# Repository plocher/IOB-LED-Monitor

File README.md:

# IOB-LED-Monitor
## License: CERN Open Hardware Licence v1.2

IOB LED Monitor daughterboard

Active-Low LED monitor for I/O pin signal debugging.
(LED is on when pin is 0v, off when pin is at Vcc)

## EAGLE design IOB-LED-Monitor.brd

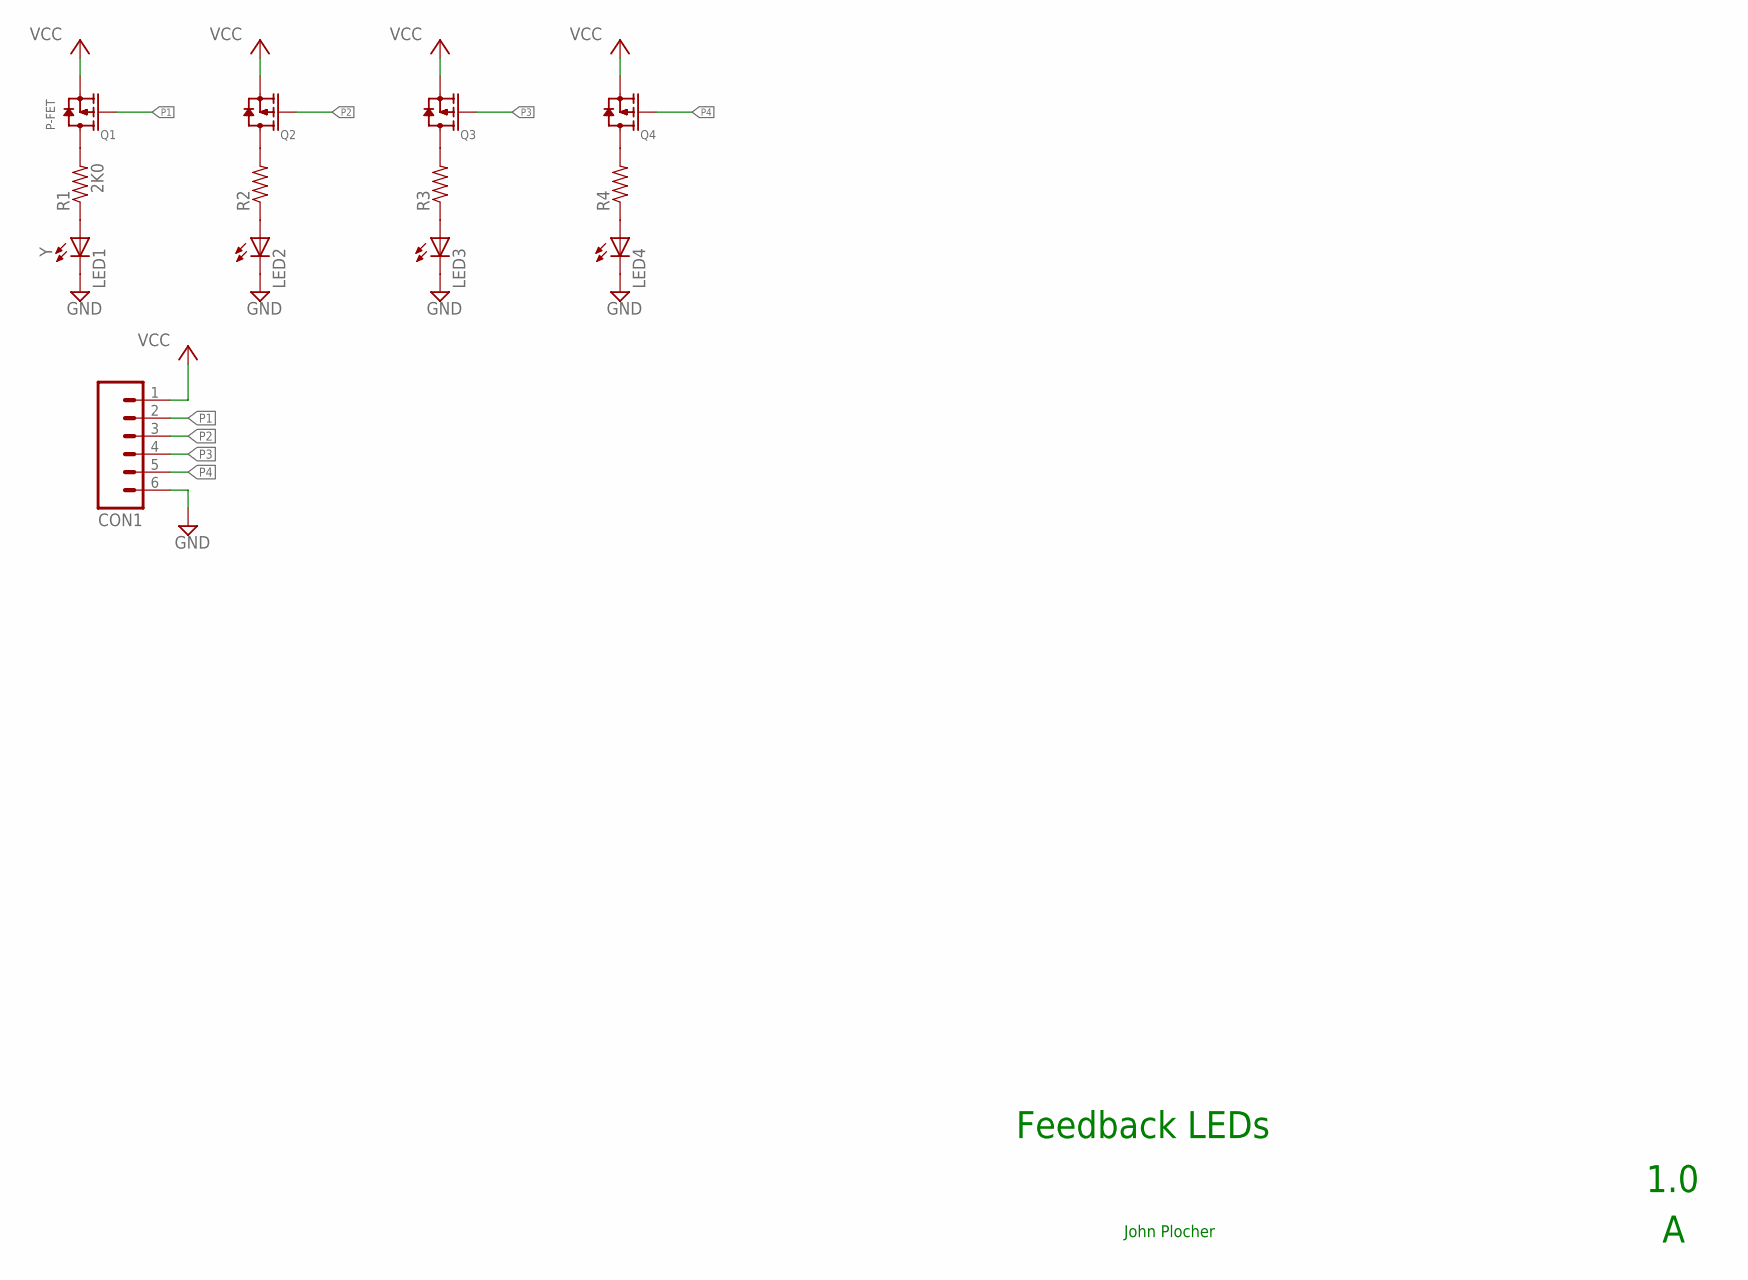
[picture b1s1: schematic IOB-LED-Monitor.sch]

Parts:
CON1: CONNECTOR-M06LOCK; 1X06_LOCK
LED1, LED2, LED3, LED4: Y; 0603-LED
Q1, Q2, Q3, Q4: P-FET; SOT23
R1, R2, R3, R4: 2K0; 0805-RES

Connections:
GND: CON1.6, LED1.C, LED2.C, LED3.C, LED4.C
unnamed: Q1.3 (D), R1.2
unnamed: Q2.3 (D), R2.2
unnamed: Q3.3 (D), R3.2
unnamed: Q4.3 (D), R4.2
unnamed: LED1.A, R1.1
unnamed: LED2.A, R2.1
unnamed: LED3.A, R3.1
unnamed: LED4.A, R4.1
P1: CON1.2, Q1.1 (G)
P2: CON1.3, Q2.1 (G)
P3: CON1.4, Q3.1 (G)
P4: CON1.5, Q4.1 (G)
VCC: CON1.1, Q1.2 (S), Q2.2 (S), Q3.2 (S), Q4.2 (S)

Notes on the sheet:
Feedback LEDs
1.0
John Plocher

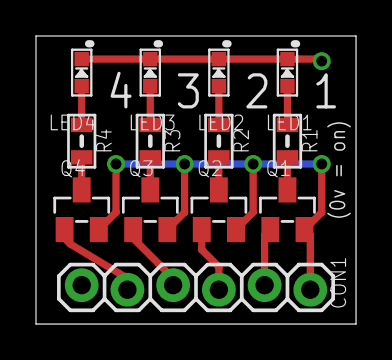
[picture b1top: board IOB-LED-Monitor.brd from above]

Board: 2 copper layers, 17.8 x 16.0 mm, 13 parts (0 on the bottom side), 14 nets.

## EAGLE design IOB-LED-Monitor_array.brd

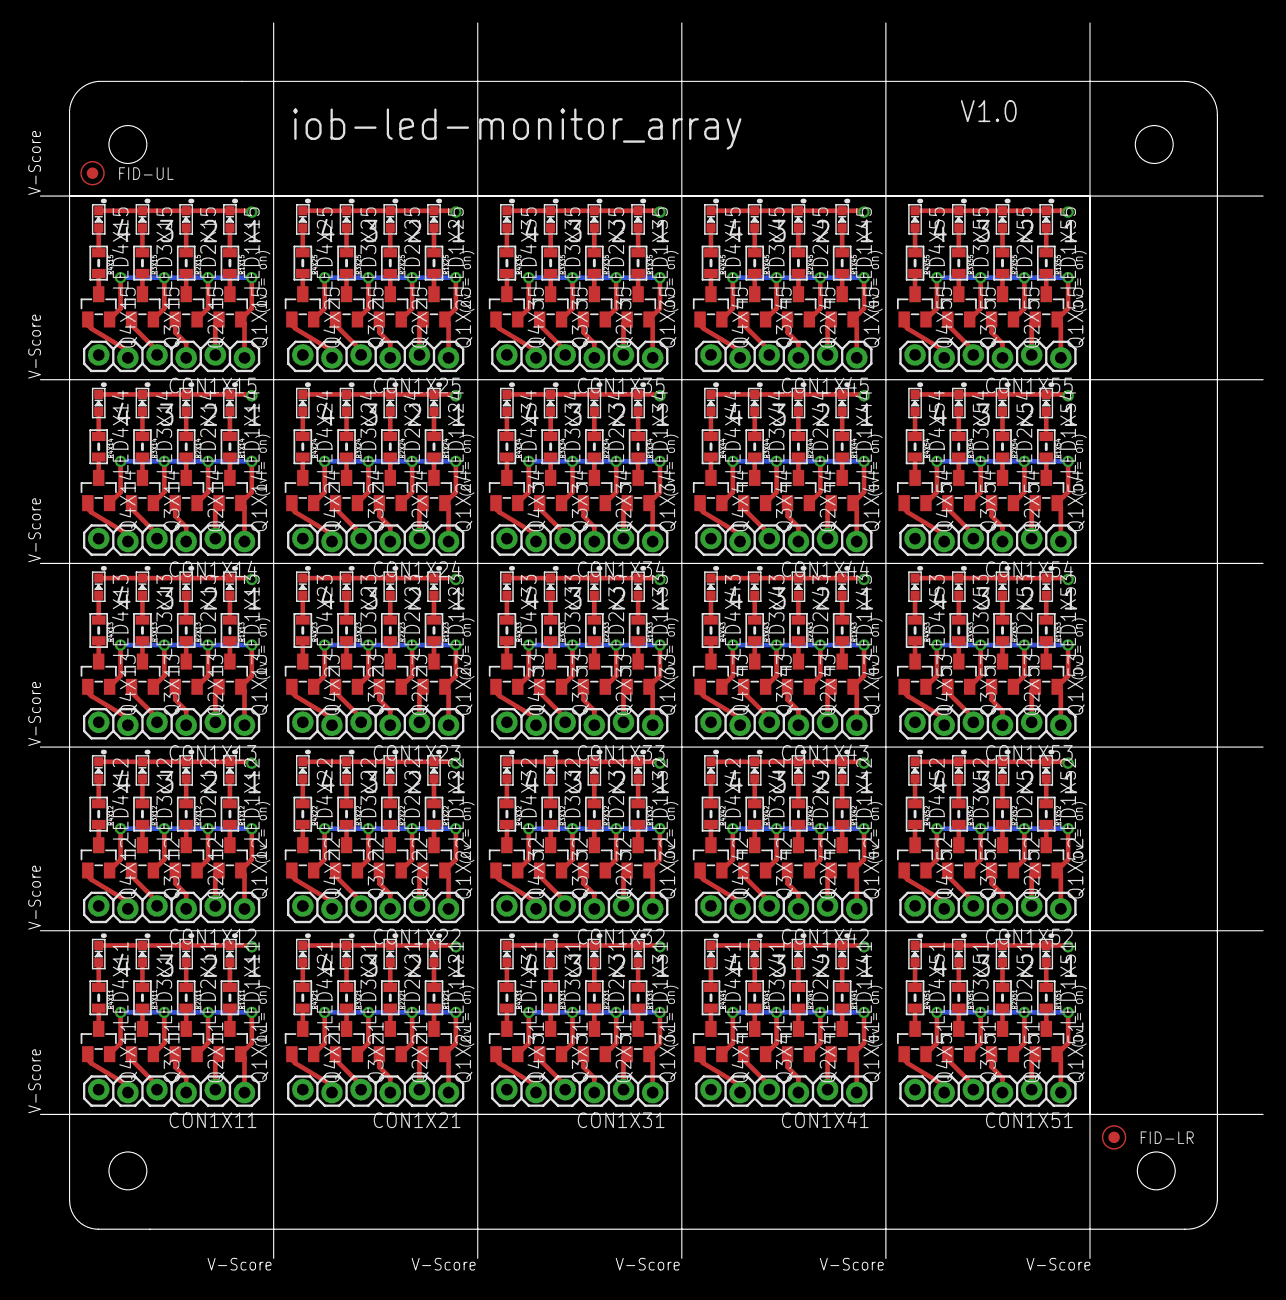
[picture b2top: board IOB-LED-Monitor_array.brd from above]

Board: 2 copper layers, 108.0 x 109.3 mm, 328 parts (0 on the bottom side), 350 nets.

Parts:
CON1X11, CON1X12, CON1X13, CON1X14, CON1X15, CON1X21, CON1X22, CON1X23, CON1X24, CON1X25, CON1X31, CON1X32, CON1X33, CON1X34, CON1X35, CON1X41, CON1X42, CON1X43, CON1X44, CON1X45, CON1X51, CON1X52, CON1X53, CON1X54, CON1X55: 1X06_LOCK
FID-LR: FIDUCIAL_1MM
FID-UL: FIDUCIAL_1MM
LED1X11, LED1X12, LED1X13, LED1X14, LED1X15, LED1X21, LED1X22, LED1X23, LED1X24, LED1X25, LED1X31, LED1X32, LED1X33, LED1X34, LED1X35, LED1X41, LED1X42, LED1X43, LED1X44, LED1X45, LED1X51, LED1X52, LED1X53, LED1X54, LED1X55, LED2X11, LED2X12, LED2X13, LED2X14, LED2X15, LED2X21, LED2X22, LED2X23, LED2X24, LED2X25, LED2X31, LED2X32, LED2X33, LED2X34, LED2X35, LED2X41, LED2X42, LED2X43, LED2X44, LED2X45, LED2X51, LED2X52, LED2X53, LED2X54, LED2X55, LED3X11, LED3X12, LED3X13, LED3X14, LED3X15, LED3X21, LED3X22, LED3X23, LED3X24, LED3X25, LED3X31, LED3X32, LED3X33, LED3X34, LED3X35, LED3X41, LED3X42, LED3X43, LED3X44, LED3X45, LED3X51, LED3X52, LED3X53, LED3X54, LED3X55, LED4X11, LED4X12, LED4X13, LED4X14, LED4X15, LED4X21, LED4X22, LED4X23, LED4X24, LED4X25, LED4X31, LED4X32, LED4X33, LED4X34, LED4X35, LED4X41, LED4X42, LED4X43, LED4X44, LED4X45, LED4X51, LED4X52, LED4X53, LED4X54, LED4X55: Y; 0603-LED
Q1X11, Q1X12, Q1X13, Q1X14, Q1X15, Q1X21, Q1X22, Q1X23, Q1X24, Q1X25, Q1X31, Q1X32, Q1X33, Q1X34, Q1X35, Q1X41, Q1X42, Q1X43, Q1X44, Q1X45, Q1X51, Q1X52, Q1X53, Q1X54, Q1X55, Q2X11, Q2X12, Q2X13, Q2X14, Q2X15, Q2X21, Q2X22, Q2X23, Q2X24, Q2X25, Q2X31, Q2X32, Q2X33, Q2X34, Q2X35, Q2X41, Q2X42, Q2X43, Q2X44, Q2X45, Q2X51, Q2X52, Q2X53, Q2X54, Q2X55, Q3X11, Q3X12, Q3X13, Q3X14, Q3X15, Q3X21, Q3X22, Q3X23, Q3X24, Q3X25, Q3X31, Q3X32, Q3X33, Q3X34, Q3X35, Q3X41, Q3X42, Q3X43, Q3X44, Q3X45, Q3X51, Q3X52, Q3X53, Q3X54, Q3X55, Q4X11, Q4X12, Q4X13, Q4X14, Q4X15, Q4X21, Q4X22, Q4X23, Q4X24, Q4X25, Q4X31, Q4X32, Q4X33, Q4X34, Q4X35, Q4X41, Q4X42, Q4X43, Q4X44, Q4X45, Q4X51, Q4X52, Q4X53, Q4X54, Q4X55: P-FET; SOT23
R1X11, R1X12, R1X13, R1X14, R1X15, R1X21, R1X22, R1X23, R1X24, R1X25, R1X31, R1X32, R1X33, R1X34, R1X35, R1X41, R1X42, R1X43, R1X44, R1X45, R1X51, R1X52, R1X53, R1X54, R1X55, R2X11, R2X12, R2X13, R2X14, R2X15, R2X21, R2X22, R2X23, R2X24, R2X25, R2X31, R2X32, R2X33, R2X34, R2X35, R2X41, R2X42, R2X43, R2X44, R2X45, R2X51, R2X52, R2X53, R2X54, R2X55, R3X11, R3X12, R3X13, R3X14, R3X15, R3X21, R3X22, R3X23, R3X24, R3X25, R3X31, R3X32, R3X33, R3X34, R3X35, R3X41, R3X42, R3X43, R3X44, R3X45, R3X51, R3X52, R3X53, R3X54, R3X55, R4X11, R4X12, R4X13, R4X14, R4X15, R4X21, R4X22, R4X23, R4X24, R4X25, R4X31, R4X32, R4X33, R4X34, R4X35, R4X41, R4X42, R4X43, R4X44, R4X45, R4X51, R4X52, R4X53, R4X54, R4X55: 2K0; 0805-RES
R4X1: BOARD-SEEED10X10

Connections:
GNDX11: CON1X11.6, LED1X11.C, LED2X11.C, LED3X11.C, LED4X11.C
GNDX12: CON1X12.6, LED1X12.C, LED2X12.C, LED3X12.C, LED4X12.C
GNDX13: CON1X13.6, LED1X13.C, LED2X13.C, LED3X13.C, LED4X13.C
GNDX14: CON1X14.6, LED1X14.C, LED2X14.C, LED3X14.C, LED4X14.C
GNDX15: CON1X15.6, LED1X15.C, LED2X15.C, LED3X15.C, LED4X15.C
GNDX21: CON1X21.6, LED1X21.C, LED2X21.C, LED3X21.C, LED4X21.C
GNDX22: CON1X22.6, LED1X22.C, LED2X22.C, LED3X22.C, LED4X22.C
GNDX23: CON1X23.6, LED1X23.C, LED2X23.C, LED3X23.C, LED4X23.C
GNDX24: CON1X24.6, LED1X24.C, LED2X24.C, LED3X24.C, LED4X24.C
GNDX25: CON1X25.6, LED1X25.C, LED2X25.C, LED3X25.C, LED4X25.C
GNDX31: CON1X31.6, LED1X31.C, LED2X31.C, LED3X31.C, LED4X31.C
GNDX32: CON1X32.6, LED1X32.C, LED2X32.C, LED3X32.C, LED4X32.C
GNDX33: CON1X33.6, LED1X33.C, LED2X33.C, LED3X33.C, LED4X33.C
GNDX34: CON1X34.6, LED1X34.C, LED2X34.C, LED3X34.C, LED4X34.C
GNDX35: CON1X35.6, LED1X35.C, LED2X35.C, LED3X35.C, LED4X35.C
GNDX41: CON1X41.6, LED1X41.C, LED2X41.C, LED3X41.C, LED4X41.C
GNDX42: CON1X42.6, LED1X42.C, LED2X42.C, LED3X42.C, LED4X42.C
GNDX43: CON1X43.6, LED1X43.C, LED2X43.C, LED3X43.C, LED4X43.C
GNDX44: CON1X44.6, LED1X44.C, LED2X44.C, LED3X44.C, LED4X44.C
GNDX45: CON1X45.6, LED1X45.C, LED2X45.C, LED3X45.C, LED4X45.C
GNDX51: CON1X51.6, LED1X51.C, LED2X51.C, LED3X51.C, LED4X51.C
GNDX52: CON1X52.6, LED1X52.C, LED2X52.C, LED3X52.C, LED4X52.C
GNDX53: CON1X53.6, LED1X53.C, LED2X53.C, LED3X53.C, LED4X53.C
GNDX54: CON1X54.6, LED1X54.C, LED2X54.C, LED3X54.C, LED4X54.C
GNDX55: CON1X55.6, LED1X55.C, LED2X55.C, LED3X55.C, LED4X55.C
unnamed: Q1X11.3, R1X11.2
unnamed: Q1X12.3, R1X12.2
unnamed: Q1X13.3, R1X13.2
unnamed: Q1X14.3, R1X14.2
unnamed: Q1X15.3, R1X15.2
unnamed: Q1X21.3, R1X21.2
unnamed: Q1X22.3, R1X22.2
unnamed: Q1X23.3, R1X23.2
unnamed: Q1X24.3, R1X24.2
unnamed: Q1X25.3, R1X25.2
unnamed: Q1X31.3, R1X31.2
unnamed: Q1X32.3, R1X32.2
unnamed: Q1X33.3, R1X33.2
unnamed: Q1X34.3, R1X34.2
unnamed: Q1X35.3, R1X35.2
unnamed: Q1X41.3, R1X41.2
unnamed: Q1X42.3, R1X42.2
unnamed: Q1X43.3, R1X43.2
unnamed: Q1X44.3, R1X44.2
unnamed: Q1X45.3, R1X45.2
unnamed: Q1X51.3, R1X51.2
unnamed: Q1X52.3, R1X52.2
unnamed: Q1X53.3, R1X53.2
unnamed: Q1X54.3, R1X54.2
unnamed: Q1X55.3, R1X55.2
unnamed: Q2X11.3, R2X11.2
unnamed: Q2X12.3, R2X12.2
unnamed: Q2X13.3, R2X13.2
unnamed: Q2X14.3, R2X14.2
unnamed: Q2X15.3, R2X15.2
unnamed: Q2X21.3, R2X21.2
unnamed: Q2X22.3, R2X22.2
unnamed: Q2X23.3, R2X23.2
unnamed: Q2X24.3, R2X24.2
unnamed: Q2X25.3, R2X25.2
unnamed: Q2X31.3, R2X31.2
unnamed: Q2X32.3, R2X32.2
unnamed: Q2X33.3, R2X33.2
unnamed: Q2X34.3, R2X34.2
unnamed: Q2X35.3, R2X35.2
unnamed: Q2X41.3, R2X41.2
unnamed: Q2X42.3, R2X42.2
unnamed: Q2X43.3, R2X43.2
unnamed: Q2X44.3, R2X44.2
unnamed: Q2X45.3, R2X45.2
unnamed: Q2X51.3, R2X51.2
unnamed: Q2X52.3, R2X52.2
unnamed: Q2X53.3, R2X53.2
unnamed: Q2X54.3, R2X54.2
unnamed: Q2X55.3, R2X55.2
unnamed: Q3X11.3, R3X11.2
unnamed: Q3X12.3, R3X12.2
unnamed: Q3X13.3, R3X13.2
unnamed: Q3X14.3, R3X14.2
unnamed: Q3X15.3, R3X15.2
unnamed: Q3X21.3, R3X21.2
unnamed: Q3X22.3, R3X22.2
unnamed: Q3X23.3, R3X23.2
unnamed: Q3X24.3, R3X24.2
unnamed: Q3X25.3, R3X25.2
unnamed: Q3X31.3, R3X31.2
unnamed: Q3X32.3, R3X32.2
unnamed: Q3X33.3, R3X33.2
unnamed: Q3X34.3, R3X34.2
unnamed: Q3X35.3, R3X35.2
unnamed: Q3X41.3, R3X41.2
unnamed: Q3X42.3, R3X42.2
unnamed: Q3X43.3, R3X43.2
unnamed: Q3X44.3, R3X44.2
unnamed: Q3X45.3, R3X45.2
unnamed: Q3X51.3, R3X51.2
unnamed: Q3X52.3, R3X52.2
unnamed: Q3X53.3, R3X53.2
unnamed: Q3X54.3, R3X54.2
unnamed: Q3X55.3, R3X55.2
unnamed: Q4X11.3, R4X11.2
unnamed: Q4X12.3, R4X12.2
unnamed: Q4X13.3, R4X13.2
unnamed: Q4X14.3, R4X14.2
unnamed: Q4X15.3, R4X15.2
unnamed: Q4X21.3, R4X21.2
unnamed: Q4X22.3, R4X22.2
unnamed: Q4X23.3, R4X23.2
unnamed: Q4X24.3, R4X24.2
unnamed: Q4X25.3, R4X25.2
unnamed: Q4X31.3, R4X31.2
unnamed: Q4X32.3, R4X32.2
unnamed: Q4X33.3, R4X33.2
unnamed: Q4X34.3, R4X34.2
unnamed: Q4X35.3, R4X35.2
unnamed: Q4X41.3, R4X41.2
unnamed: Q4X42.3, R4X42.2
unnamed: Q4X43.3, R4X43.2
unnamed: Q4X44.3, R4X44.2
unnamed: Q4X45.3, R4X45.2
unnamed: Q4X51.3, R4X51.2
unnamed: Q4X52.3, R4X52.2
unnamed: Q4X53.3, R4X53.2
unnamed: Q4X54.3, R4X54.2
unnamed: Q4X55.3, R4X55.2
unnamed: LED1X11.A, R1X11.1
unnamed: LED1X12.A, R1X12.1
unnamed: LED1X13.A, R1X13.1
unnamed: LED1X14.A, R1X14.1
unnamed: LED1X15.A, R1X15.1
unnamed: LED1X21.A, R1X21.1
unnamed: LED1X22.A, R1X22.1
unnamed: LED1X23.A, R1X23.1
unnamed: LED1X24.A, R1X24.1
unnamed: LED1X25.A, R1X25.1
unnamed: LED1X31.A, R1X31.1
unnamed: LED1X32.A, R1X32.1
unnamed: LED1X33.A, R1X33.1
unnamed: LED1X34.A, R1X34.1
unnamed: LED1X35.A, R1X35.1
unnamed: LED1X41.A, R1X41.1
unnamed: LED1X42.A, R1X42.1
unnamed: LED1X43.A, R1X43.1
unnamed: LED1X44.A, R1X44.1
unnamed: LED1X45.A, R1X45.1
unnamed: LED1X51.A, R1X51.1
unnamed: LED1X52.A, R1X52.1
unnamed: LED1X53.A, R1X53.1
unnamed: LED1X54.A, R1X54.1
unnamed: LED1X55.A, R1X55.1
unnamed: LED2X11.A, R2X11.1
unnamed: LED2X12.A, R2X12.1
unnamed: LED2X13.A, R2X13.1
unnamed: LED2X14.A, R2X14.1
unnamed: LED2X15.A, R2X15.1
unnamed: LED2X21.A, R2X21.1
unnamed: LED2X22.A, R2X22.1
unnamed: LED2X23.A, R2X23.1
unnamed: LED2X24.A, R2X24.1
unnamed: LED2X25.A, R2X25.1
unnamed: LED2X31.A, R2X31.1
unnamed: LED2X32.A, R2X32.1
unnamed: LED2X33.A, R2X33.1
unnamed: LED2X34.A, R2X34.1
unnamed: LED2X35.A, R2X35.1
unnamed: LED2X41.A, R2X41.1
unnamed: LED2X42.A, R2X42.1
unnamed: LED2X43.A, R2X43.1
unnamed: LED2X44.A, R2X44.1
unnamed: LED2X45.A, R2X45.1
unnamed: LED2X51.A, R2X51.1
unnamed: LED2X52.A, R2X52.1
unnamed: LED2X53.A, R2X53.1
unnamed: LED2X54.A, R2X54.1
unnamed: LED2X55.A, R2X55.1
unnamed: LED3X11.A, R3X11.1
unnamed: LED3X12.A, R3X12.1
unnamed: LED3X13.A, R3X13.1
unnamed: LED3X14.A, R3X14.1
unnamed: LED3X15.A, R3X15.1
unnamed: LED3X21.A, R3X21.1
unnamed: LED3X22.A, R3X22.1
unnamed: LED3X23.A, R3X23.1
unnamed: LED3X24.A, R3X24.1
unnamed: LED3X25.A, R3X25.1
unnamed: LED3X31.A, R3X31.1
unnamed: LED3X32.A, R3X32.1
unnamed: LED3X33.A, R3X33.1
unnamed: LED3X34.A, R3X34.1
unnamed: LED3X35.A, R3X35.1
unnamed: LED3X41.A, R3X41.1
unnamed: LED3X42.A, R3X42.1
unnamed: LED3X43.A, R3X43.1
unnamed: LED3X44.A, R3X44.1
unnamed: LED3X45.A, R3X45.1
unnamed: LED3X51.A, R3X51.1
unnamed: LED3X52.A, R3X52.1
unnamed: LED3X53.A, R3X53.1
unnamed: LED3X54.A, R3X54.1
unnamed: LED3X55.A, R3X55.1
unnamed: LED4X11.A, R4X11.1
unnamed: LED4X12.A, R4X12.1
unnamed: LED4X13.A, R4X13.1
unnamed: LED4X14.A, R4X14.1
unnamed: LED4X15.A, R4X15.1
unnamed: LED4X21.A, R4X21.1
unnamed: LED4X22.A, R4X22.1
unnamed: LED4X23.A, R4X23.1
unnamed: LED4X24.A, R4X24.1
unnamed: LED4X25.A, R4X25.1
unnamed: LED4X31.A, R4X31.1
unnamed: LED4X32.A, R4X32.1
unnamed: LED4X33.A, R4X33.1
unnamed: LED4X34.A, R4X34.1
unnamed: LED4X35.A, R4X35.1
unnamed: LED4X41.A, R4X41.1
unnamed: LED4X42.A, R4X42.1
unnamed: LED4X43.A, R4X43.1
unnamed: LED4X44.A, R4X44.1
unnamed: LED4X45.A, R4X45.1
unnamed: LED4X51.A, R4X51.1
unnamed: LED4X52.A, R4X52.1
unnamed: LED4X53.A, R4X53.1
unnamed: LED4X54.A, R4X54.1
unnamed: LED4X55.A, R4X55.1
P1X11: CON1X11.2, Q1X11.1
P1X12: CON1X12.2, Q1X12.1
P1X13: CON1X13.2, Q1X13.1
P1X14: CON1X14.2, Q1X14.1
P1X15: CON1X15.2, Q1X15.1
P1X21: CON1X21.2, Q1X21.1
P1X22: CON1X22.2, Q1X22.1
P1X23: CON1X23.2, Q1X23.1
P1X24: CON1X24.2, Q1X24.1
P1X25: CON1X25.2, Q1X25.1
P1X31: CON1X31.2, Q1X31.1
P1X32: CON1X32.2, Q1X32.1
P1X33: CON1X33.2, Q1X33.1
P1X34: CON1X34.2, Q1X34.1
P1X35: CON1X35.2, Q1X35.1
P1X41: CON1X41.2, Q1X41.1
P1X42: CON1X42.2, Q1X42.1
P1X43: CON1X43.2, Q1X43.1
P1X44: CON1X44.2, Q1X44.1
P1X45: CON1X45.2, Q1X45.1
P1X51: CON1X51.2, Q1X51.1
P1X52: CON1X52.2, Q1X52.1
P1X53: CON1X53.2, Q1X53.1
P1X54: CON1X54.2, Q1X54.1
P1X55: CON1X55.2, Q1X55.1
P2X11: CON1X11.3, Q2X11.1
P2X12: CON1X12.3, Q2X12.1
P2X13: CON1X13.3, Q2X13.1
P2X14: CON1X14.3, Q2X14.1
P2X15: CON1X15.3, Q2X15.1
P2X21: CON1X21.3, Q2X21.1
P2X22: CON1X22.3, Q2X22.1
P2X23: CON1X23.3, Q2X23.1
P2X24: CON1X24.3, Q2X24.1
P2X25: CON1X25.3, Q2X25.1
P2X31: CON1X31.3, Q2X31.1
P2X32: CON1X32.3, Q2X32.1
P2X33: CON1X33.3, Q2X33.1
P2X34: CON1X34.3, Q2X34.1
P2X35: CON1X35.3, Q2X35.1
P2X41: CON1X41.3, Q2X41.1
P2X42: CON1X42.3, Q2X42.1
P2X43: CON1X43.3, Q2X43.1
P2X44: CON1X44.3, Q2X44.1
P2X45: CON1X45.3, Q2X45.1
P2X51: CON1X51.3, Q2X51.1
P2X52: CON1X52.3, Q2X52.1
P2X53: CON1X53.3, Q2X53.1
P2X54: CON1X54.3, Q2X54.1
P2X55: CON1X55.3, Q2X55.1
P3X11: CON1X11.4, Q3X11.1
P3X12: CON1X12.4, Q3X12.1
P3X13: CON1X13.4, Q3X13.1
P3X14: CON1X14.4, Q3X14.1
P3X15: CON1X15.4, Q3X15.1
P3X21: CON1X21.4, Q3X21.1
P3X22: CON1X22.4, Q3X22.1
P3X23: CON1X23.4, Q3X23.1
P3X24: CON1X24.4, Q3X24.1
P3X25: CON1X25.4, Q3X25.1
P3X31: CON1X31.4, Q3X31.1
P3X32: CON1X32.4, Q3X32.1
P3X33: CON1X33.4, Q3X33.1
P3X34: CON1X34.4, Q3X34.1
P3X35: CON1X35.4, Q3X35.1
P3X41: CON1X41.4, Q3X41.1
P3X42: CON1X42.4, Q3X42.1
P3X43: CON1X43.4, Q3X43.1
P3X44: CON1X44.4, Q3X44.1
P3X45: CON1X45.4, Q3X45.1
P3X51: CON1X51.4, Q3X51.1
P3X52: CON1X52.4, Q3X52.1
P3X53: CON1X53.4, Q3X53.1
P3X54: CON1X54.4, Q3X54.1
P3X55: CON1X55.4, Q3X55.1
P4X11: CON1X11.5, Q4X11.1
P4X12: CON1X12.5, Q4X12.1
P4X13: CON1X13.5, Q4X13.1
P4X14: CON1X14.5, Q4X14.1
P4X15: CON1X15.5, Q4X15.1
P4X21: CON1X21.5, Q4X21.1
P4X22: CON1X22.5, Q4X22.1
P4X23: CON1X23.5, Q4X23.1
P4X24: CON1X24.5, Q4X24.1
P4X25: CON1X25.5, Q4X25.1
P4X31: CON1X31.5, Q4X31.1
P4X32: CON1X32.5, Q4X32.1
P4X33: CON1X33.5, Q4X33.1
P4X34: CON1X34.5, Q4X34.1
P4X35: CON1X35.5, Q4X35.1
P4X41: CON1X41.5, Q4X41.1
P4X42: CON1X42.5, Q4X42.1
P4X43: CON1X43.5, Q4X43.1
P4X44: CON1X44.5, Q4X44.1
P4X45: CON1X45.5, Q4X45.1
P4X51: CON1X51.5, Q4X51.1
P4X52: CON1X52.5, Q4X52.1
P4X53: CON1X53.5, Q4X53.1
P4X54: CON1X54.5, Q4X54.1
P4X55: CON1X55.5, Q4X55.1
VCCX11: CON1X11.1, Q1X11.2, Q2X11.2, Q3X11.2, Q4X11.2
VCCX12: CON1X12.1, Q1X12.2, Q2X12.2, Q3X12.2, Q4X12.2
VCCX13: CON1X13.1, Q1X13.2, Q2X13.2, Q3X13.2, Q4X13.2
VCCX14: CON1X14.1, Q1X14.2, Q2X14.2, Q3X14.2, Q4X14.2
VCCX15: CON1X15.1, Q1X15.2, Q2X15.2, Q3X15.2, Q4X15.2
VCCX21: CON1X21.1, Q1X21.2, Q2X21.2, Q3X21.2, Q4X21.2
VCCX22: CON1X22.1, Q1X22.2, Q2X22.2, Q3X22.2, Q4X22.2
VCCX23: CON1X23.1, Q1X23.2, Q2X23.2, Q3X23.2, Q4X23.2
VCCX24: CON1X24.1, Q1X24.2, Q2X24.2, Q3X24.2, Q4X24.2
VCCX25: CON1X25.1, Q1X25.2, Q2X25.2, Q3X25.2, Q4X25.2
VCCX31: CON1X31.1, Q1X31.2, Q2X31.2, Q3X31.2, Q4X31.2
VCCX32: CON1X32.1, Q1X32.2, Q2X32.2, Q3X32.2, Q4X32.2
VCCX33: CON1X33.1, Q1X33.2, Q2X33.2, Q3X33.2, Q4X33.2
VCCX34: CON1X34.1, Q1X34.2, Q2X34.2, Q3X34.2, Q4X34.2
VCCX35: CON1X35.1, Q1X35.2, Q2X35.2, Q3X35.2, Q4X35.2
VCCX41: CON1X41.1, Q1X41.2, Q2X41.2, Q3X41.2, Q4X41.2
VCCX42: CON1X42.1, Q1X42.2, Q2X42.2, Q3X42.2, Q4X42.2
VCCX43: CON1X43.1, Q1X43.2, Q2X43.2, Q3X43.2, Q4X43.2
VCCX44: CON1X44.1, Q1X44.2, Q2X44.2, Q3X44.2, Q4X44.2
VCCX45: CON1X45.1, Q1X45.2, Q2X45.2, Q3X45.2, Q4X45.2
VCCX51: CON1X51.1, Q1X51.2, Q2X51.2, Q3X51.2, Q4X51.2
VCCX52: CON1X52.1, Q1X52.2, Q2X52.2, Q3X52.2, Q4X52.2
VCCX53: CON1X53.1, Q1X53.2, Q2X53.2, Q3X53.2, Q4X53.2
VCCX54: CON1X54.1, Q1X54.2, Q2X54.2, Q3X54.2, Q4X54.2
VCCX55: CON1X55.1, Q1X55.2, Q2X55.2, Q3X55.2, Q4X55.2

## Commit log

2020-09-05 Initial version
2020-09-05 added graphic
2020-09-11 update docs
